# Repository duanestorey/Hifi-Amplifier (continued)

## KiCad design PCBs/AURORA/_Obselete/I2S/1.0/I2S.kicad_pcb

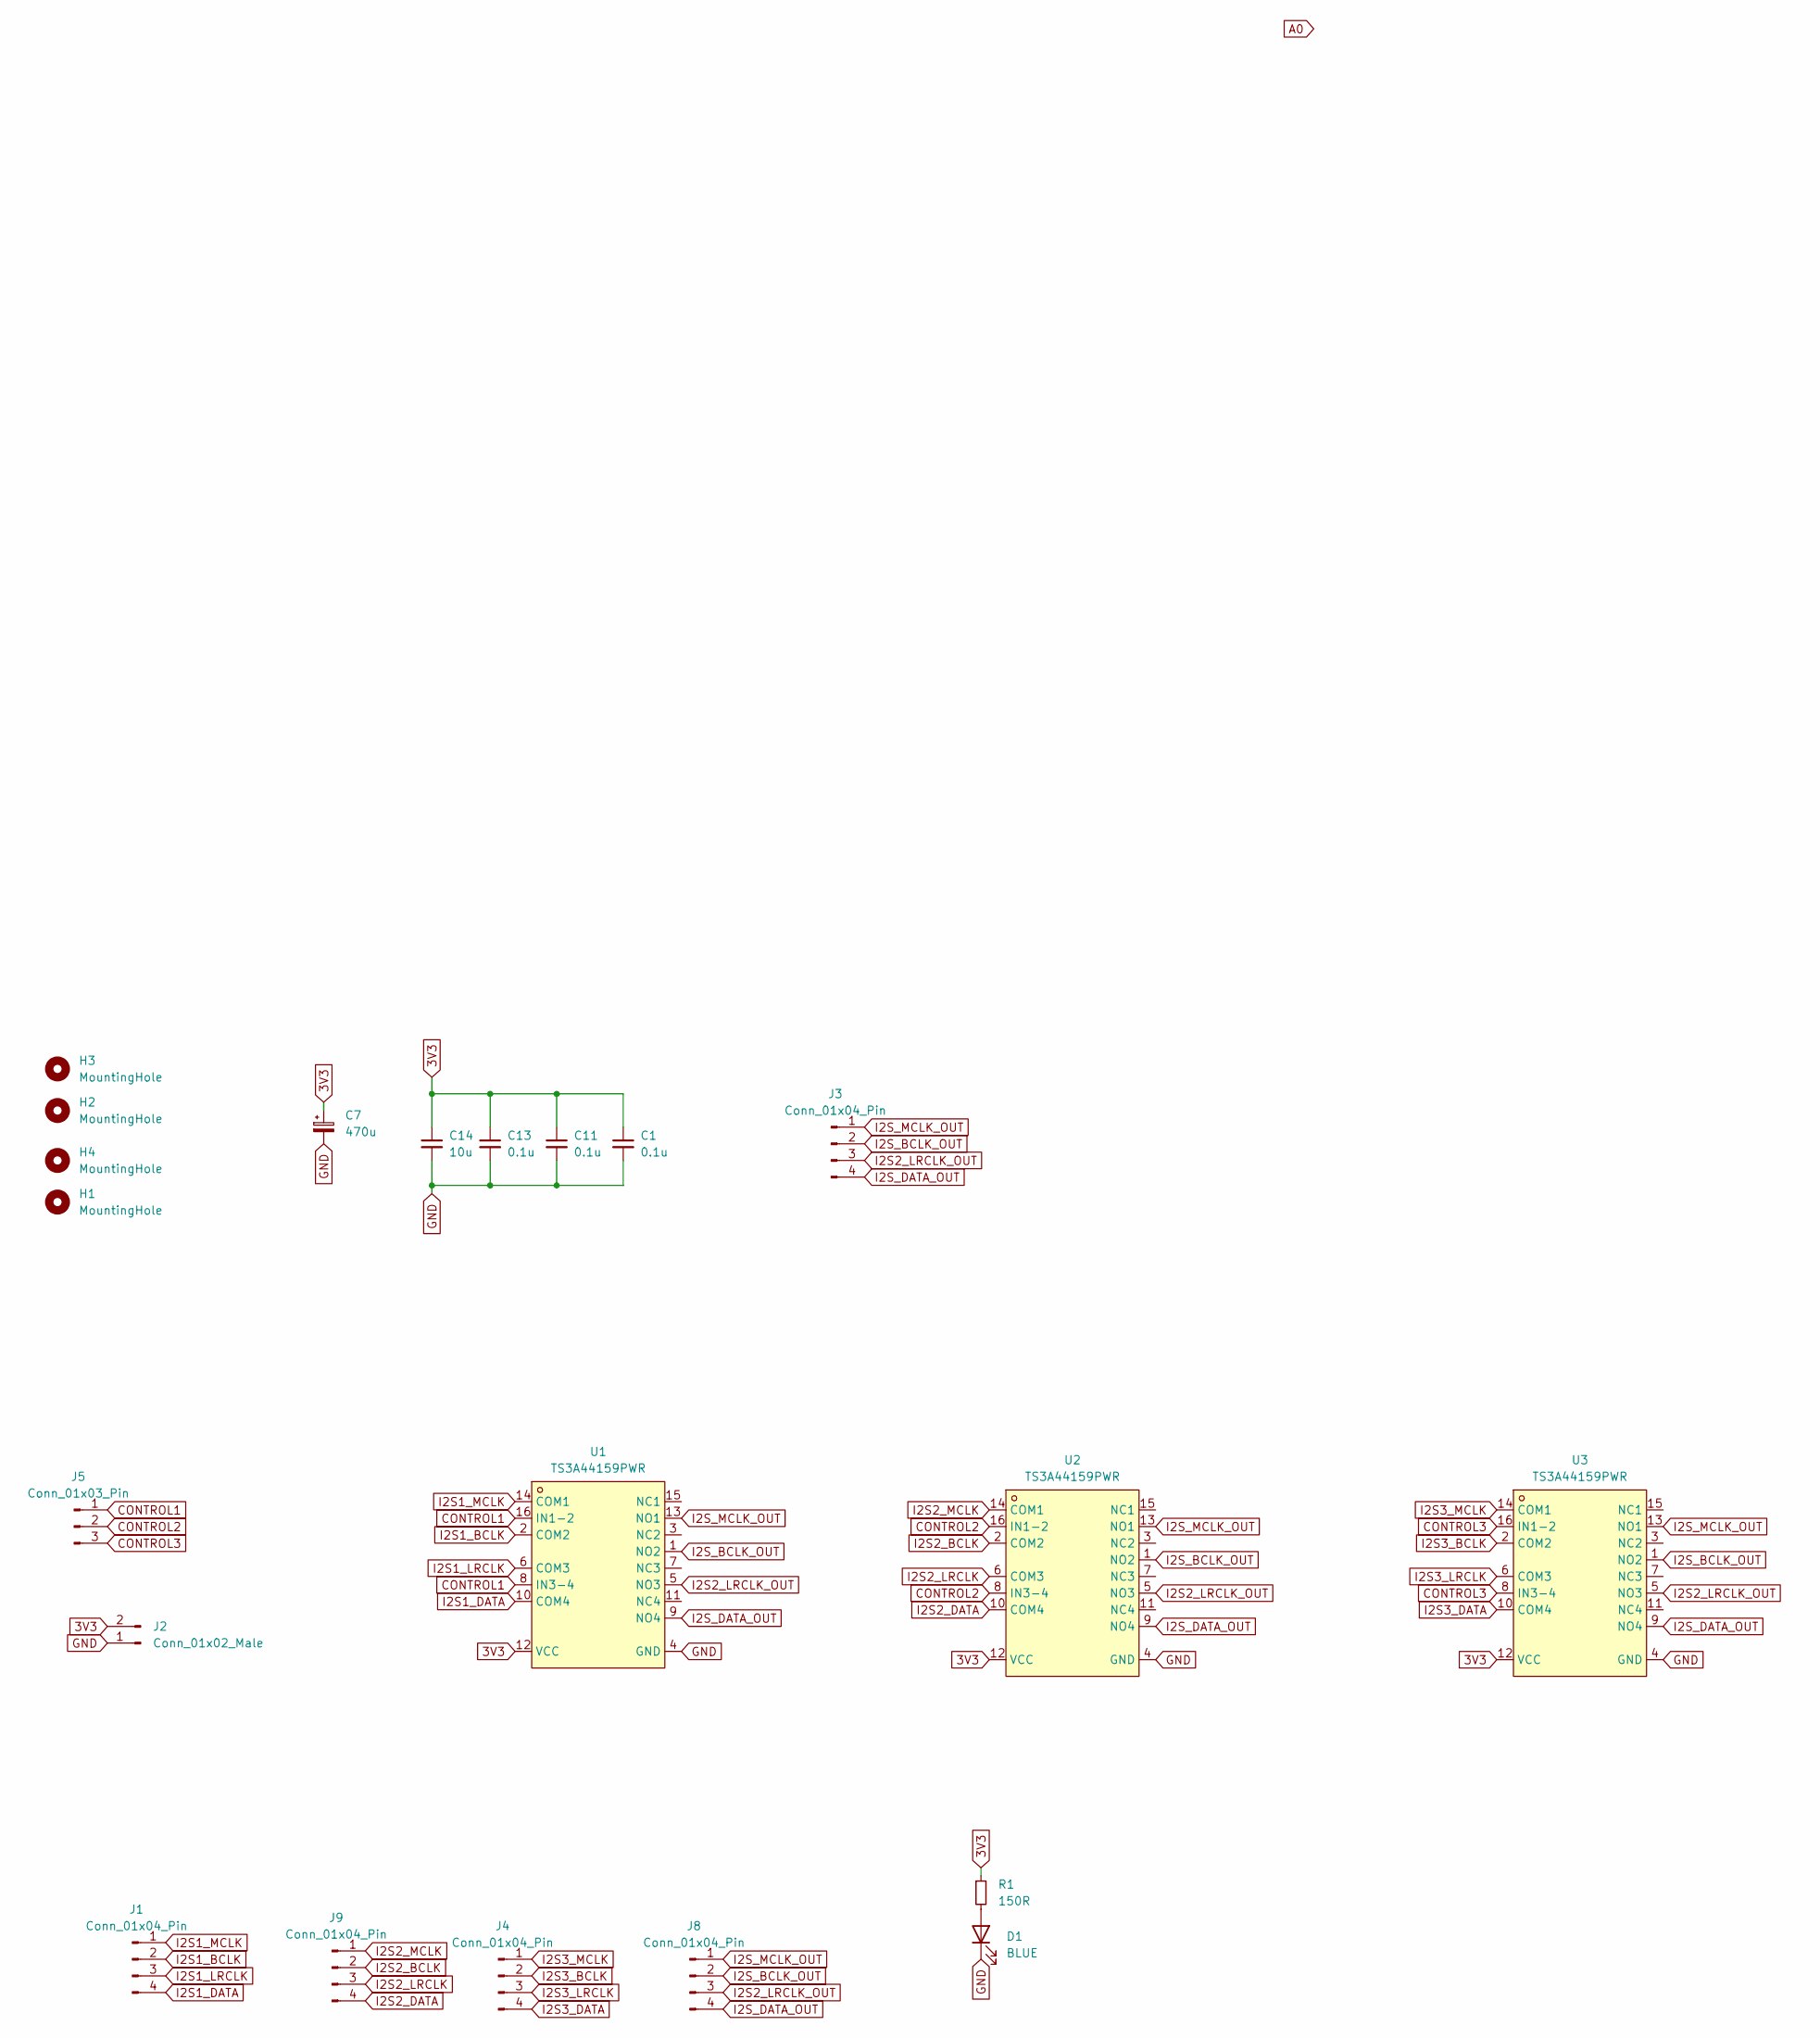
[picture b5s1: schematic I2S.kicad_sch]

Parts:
C1, C11, C13: 0.1u; C_0805_2012Metric_Pad1.18x1.45mm_HandSolder
C7: 470u; CP_Radial_D6.3mm_P2.50mm
C14: 10u; C_1206_3216Metric_Pad1.33x1.80mm_HandSolder
D1: BLUE; LED_0603_1608Metric
H1, H2, H3, H4: MountingHole; MountingHole_3.2mm_M3_DIN965_Pad_TopOnly
J1, J4, J8, J9: Conn_01x04_Pin; JST_PH_B4B-PH-K_1x04_P2.00mm_Vertical
J2: Conn_01x02_Male; JST_PH_B2B-PH-K_1x02_P2.00mm_Vertical
J3: Conn_01x04_Pin; PinHeader_1x04_P2.54mm_Vertical
J5: Conn_01x03_Pin; JST_PH_B3B-PH-K_1x03_P2.00mm_Vertical
R1: 150R; R_0603_1608Metric
U1, U2, U3: TS3A44159PWR; TSSOP-16_L5.0-W4.4-P0.65-LS6.4-BL; LCSC Part C151886

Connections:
3V3: C1.1, C7.1, C11.1, C13.1, C14.1, J2.2, R1.1, U1.12 (VCC), U2.12 (VCC), U3.12 (VCC)
CONTROL1: J5.1, U1.8 (IN3-4), U1.16 (IN1-2)
CONTROL2: J5.2, U2.8 (IN3-4), U2.16 (IN1-2)
CONTROL3: J5.3, U3.8 (IN3-4), U3.16 (IN1-2)
GND: C1.2, C7.2, C11.2, C13.2, C14.2, D1.1 (K), J2.1, U1.4 (GND), U2.4 (GND), U3.4 (GND)
I2S1_BCLK: J1.2, U1.2 (COM2)
I2S1_DATA: J1.4, U1.10 (COM4)
I2S1_LRCLK: J1.3, U1.6 (COM3)
I2S1_MCLK: J1.1, U1.14 (COM1)
I2S2_BCLK: J9.2, U2.2 (COM2)
I2S2_DATA: J9.4, U2.10 (COM4)
I2S2_LRCLK: J9.3, U2.6 (COM3)
I2S2_LRCLK_OUT: J3.3, J8.3, U1.5 (NO3), U2.5 (NO3), U3.5 (NO3)
I2S2_MCLK: J9.1, U2.14 (COM1)
I2S3_BCLK: J4.2, U3.2 (COM2)
I2S3_DATA: J4.4, U3.10 (COM4)
I2S3_LRCLK: J4.3, U3.6 (COM3)
I2S3_MCLK: J4.1, U3.14 (COM1)
I2S_BCLK_OUT: J3.2, J8.2, U1.1 (NO2), U2.1 (NO2), U3.1 (NO2)
I2S_DATA_OUT: J3.4, J8.4, U1.9 (NO4), U2.9 (NO4), U3.9 (NO4)
I2S_MCLK_OUT: J3.1, J8.1, U1.13 (NO1), U2.13 (NO1), U3.13 (NO1)
unnamed: D1.2 (A), R1.2

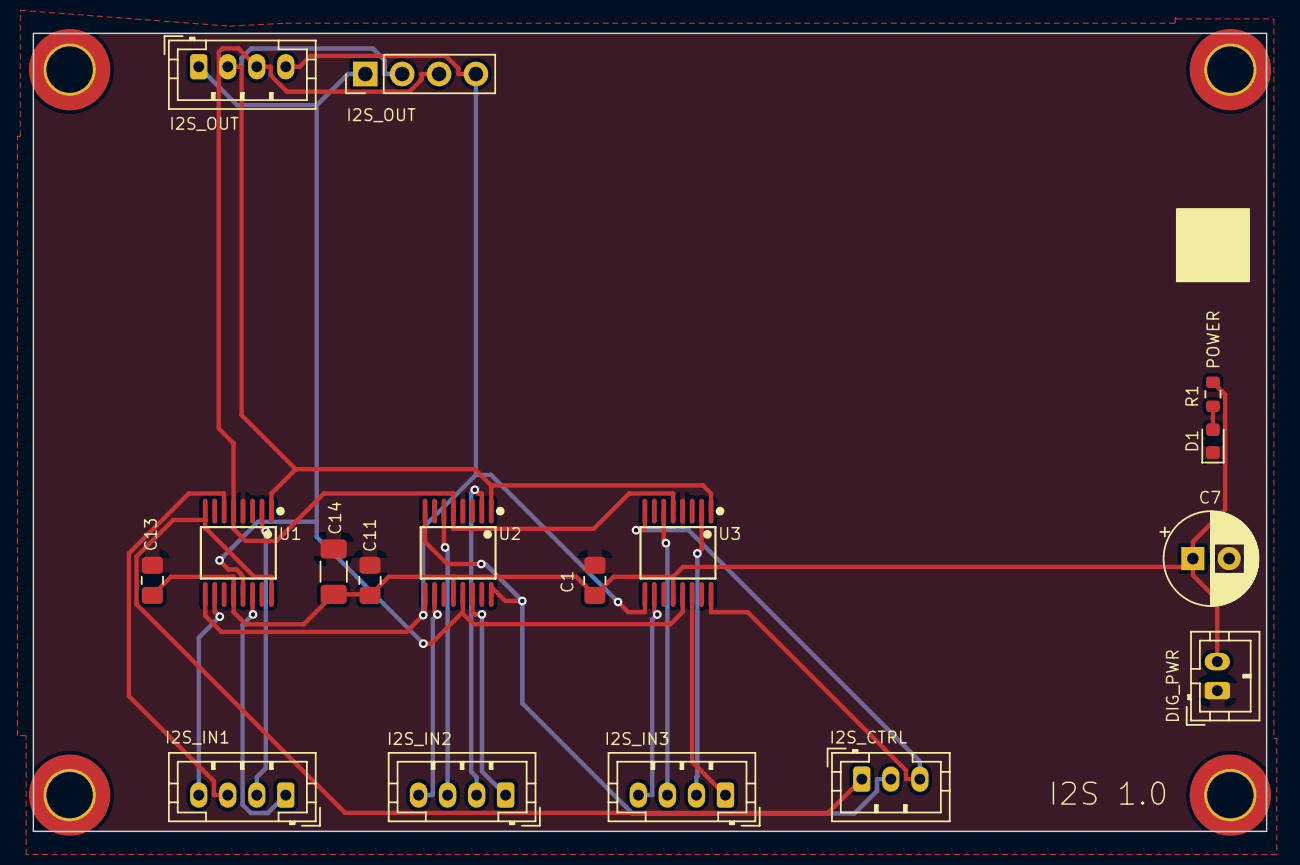
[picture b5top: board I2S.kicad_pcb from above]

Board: 2 copper layers, 85.0 x 55.0 mm, 21 parts (0 on the bottom side), 22 nets.

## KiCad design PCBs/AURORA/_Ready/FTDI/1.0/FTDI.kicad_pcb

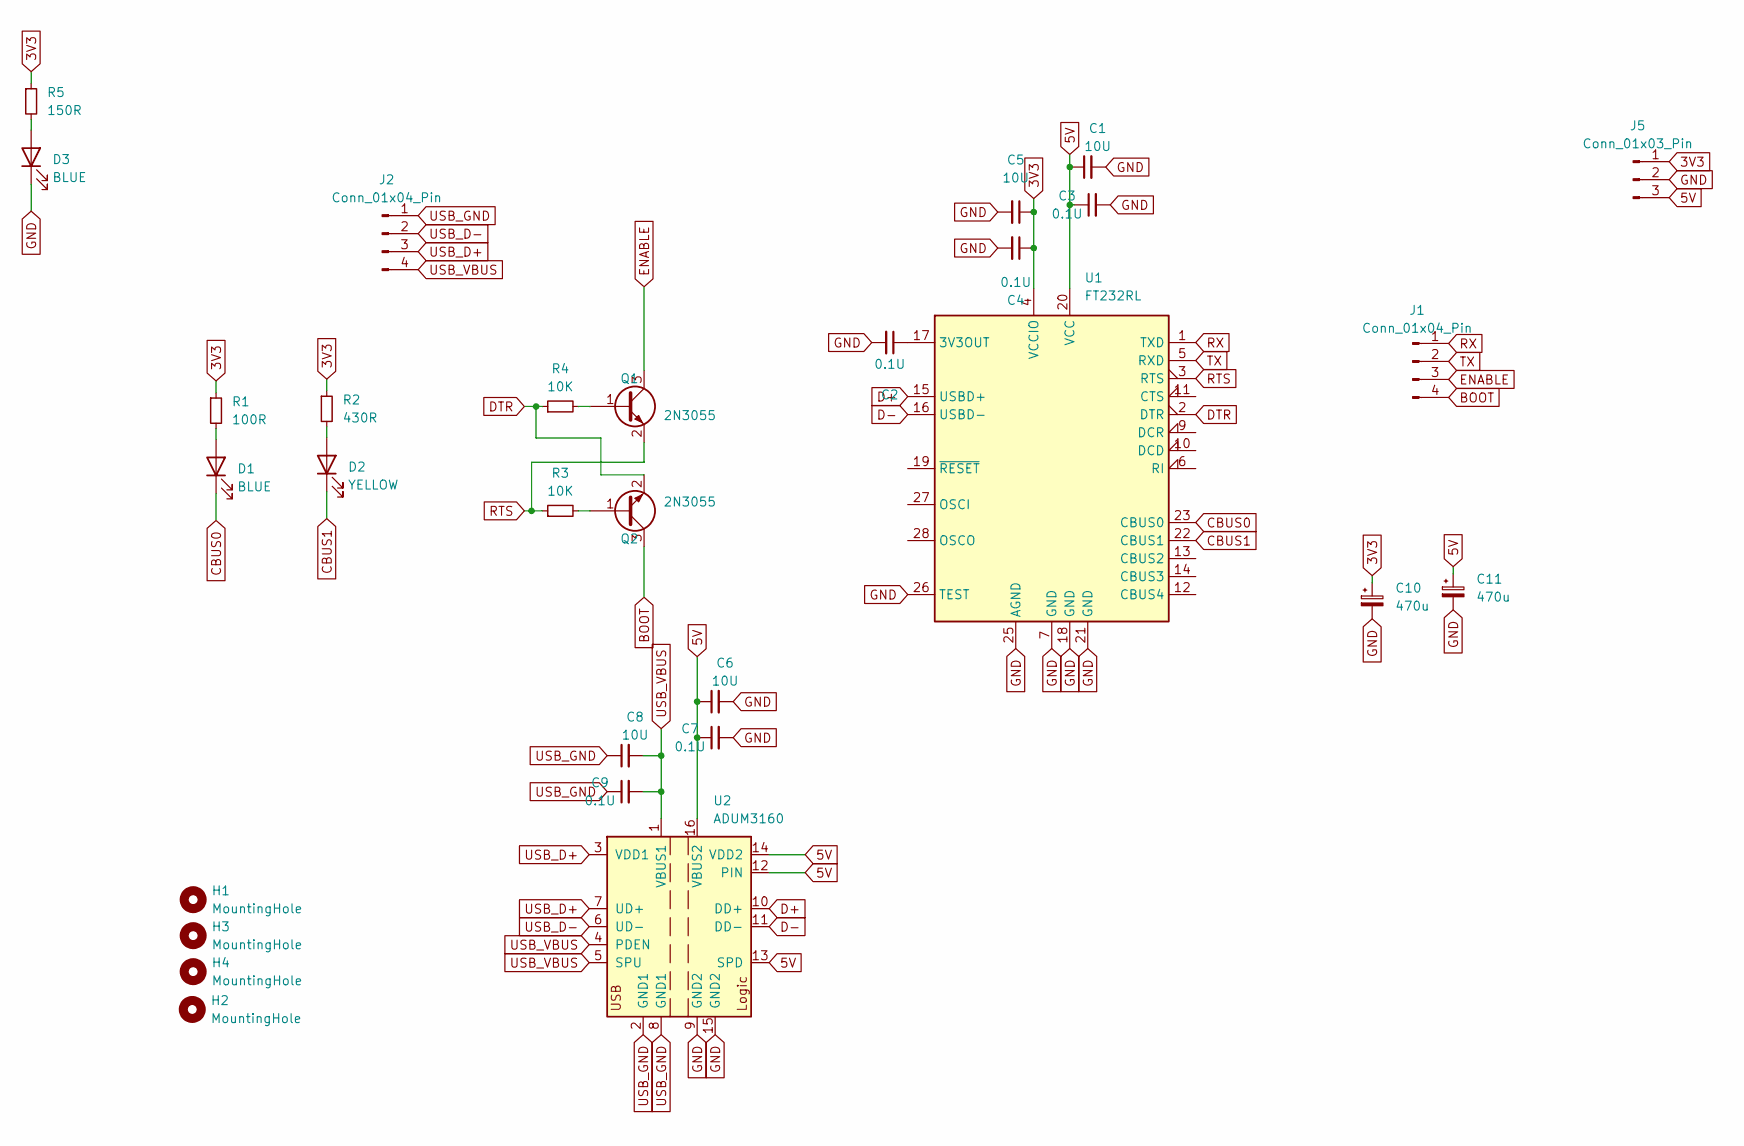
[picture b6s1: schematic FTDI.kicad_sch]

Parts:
C1, C5, C6, C8: 10U; C_1206_3216Metric_Pad1.33x1.80mm_HandSolder
C2, C3, C4, C7, C9: 0.1U; C_0805_2012Metric_Pad1.18x1.45mm_HandSolder
C10, C11: 470u; CP_Radial_D6.3mm_P2.50mm
D1, D3: BLUE; LED_0603_1608Metric_Pad1.05x0.95mm_HandSolder; LCSC XL-1608UBC-04
D2: YELLOW; LED_0603_1608Metric_Pad1.05x0.95mm_HandSolder; LCSC XL-1608UBC-04
H1, H2, H3, H4: MountingHole; MountingHole_3.2mm_M3_DIN965_Pad_TopOnly
J1, J2: Conn_01x04_Pin; JST_PH_B4B-PH-K_1x04_P2.00mm_Vertical
J5: Conn_01x03_Pin; JST_PH_B3B-PH-K_1x03_P2.00mm_Vertical
Q1, Q2: 2N3055; TSOT-23
R1: 100R; R_0603_1608Metric_Pad0.98x0.95mm_HandSolder
R2: 430R; R_0603_1608Metric_Pad0.98x0.95mm_HandSolder
R3, R4: 10K; R_0603_1608Metric_Pad0.98x0.95mm_HandSolder
R5: 150R; R_0603_1608Metric_Pad0.98x0.95mm_HandSolder
U1: FT232RL; SSOP-28_5.3x10.2mm_P0.65mm
U2: ADUM3160; SOIC-16W_7.5x10.3mm_P1.27mm; Mouser 584-ADUM3160BRWZ-R

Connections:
3V3: C4.1, C5.1, C10.1, J5.1, R1.1, R2.1, R5.1, U1.4 (VCCIO)
5V: C1.1, C3.1, C6.1, C7.1, C11.1, J5.3, U1.20 (VCC), U2.12 (PIN), U2.13 (SPD), U2.14 (VDD2), U2.16 (VBUS2)
BOOT: J1.4, Q2.3 (C)
CBUS0: D1.1 (K), U1.23 (CBUS0)
CBUS1: D2.1 (K), U1.22 (CBUS1)
D+: U1.15 (USBD+), U2.10 (DD+)
D-: U1.16 (USBD-), U2.11 (DD-)
DTR: Q2.2 (E), R4.1, U1.2 (DTR)
ENABLE: J1.3, Q1.3 (C)
GND: C1.2, C2.2, C3.2, C4.2, C5.2, C6.2, C7.2, C10.2, C11.2, D3.1 (K), J5.2, U1.7 (GND), U1.18 (GND), U1.21 (GND), U1.25 (AGND), U1.26 (TEST), U2.9 (GND2), U2.15 (GND2)
unnamed: D1.2 (A), R1.2
unnamed: D2.2 (A), R2.2
unnamed: D3.2 (A), R5.2
unnamed: Q1.1 (B), R4.2
unnamed: Q2.1 (B), R3.2
unnamed: C2.1, U1.17 (3V3OUT)
RTS: Q1.2 (E), R3.1, U1.3 (RTS)
RX: J1.1, U1.1 (TXD)
TX: J1.2, U1.5 (RXD)
USB_D+: J2.3, U2.3 (VDD1), U2.7 (UD+)
USB_D-: J2.2, U2.6 (UD-)
USB_GND: C8.1, C9.1, J2.1, U2.2 (GND1), U2.8 (GND1)
USB_VBUS: C8.2, C9.2, J2.4, U2.1 (VBUS1), U2.4 (PDEN), U2.5 (SPU)

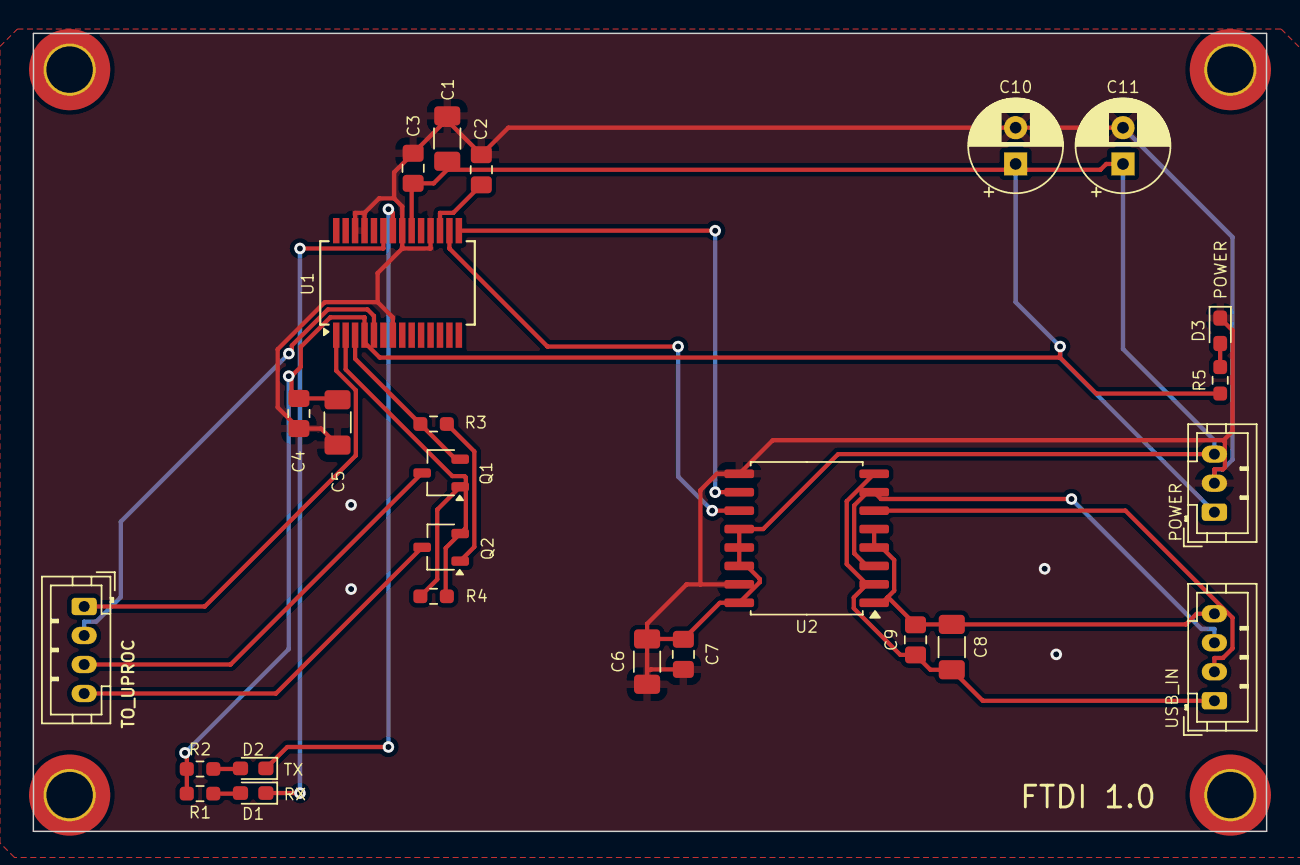
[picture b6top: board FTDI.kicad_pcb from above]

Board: 2 copper layers, 85.0 x 55.0 mm, 30 parts (0 on the bottom side), 23 nets.

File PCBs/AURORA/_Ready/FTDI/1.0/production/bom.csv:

Designator,Footprint,Quantity,Value,LCSC Part #
"C1, C5, C6, C8",1206,4,10U,
"C10, C11",CP_Radial_D6.3mm_P2.50mm,2,470u,
"C2, C3, C4, C7, C9",0805,5,0.1U,
"D1, D3",0603,2,BLUE,XL-1608UBC-04
D2,0603,1,YELLOW,XL-1608UBC-04
"H1, H2, H3, H4",MountingHole_3.2mm_M3_DIN965_Pad_TopOnly,4,MountingHole,
"J1, J2",JST_PH_B4B-PH-K_1x04_P2.00mm_Vertical,2,Conn_01x04_Pin,
J5,JST_PH_B3B-PH-K_1x03_P2.00mm_Vertical,1,Conn_01x03_Pin,
"Q1, Q2",TSOT-23,2,2N3055,
R1,0603,1,100R,
R2,0603,1,430R,
"R3, R4",0603,2,10K,
R5,0603,1,150R,
U1,SSOP-28_5.3x10.2mm_P0.65mm,1,FT232RL,
U2,SOIC-16W_7.5x10.3mm_P1.27mm,1,ADUM3160,

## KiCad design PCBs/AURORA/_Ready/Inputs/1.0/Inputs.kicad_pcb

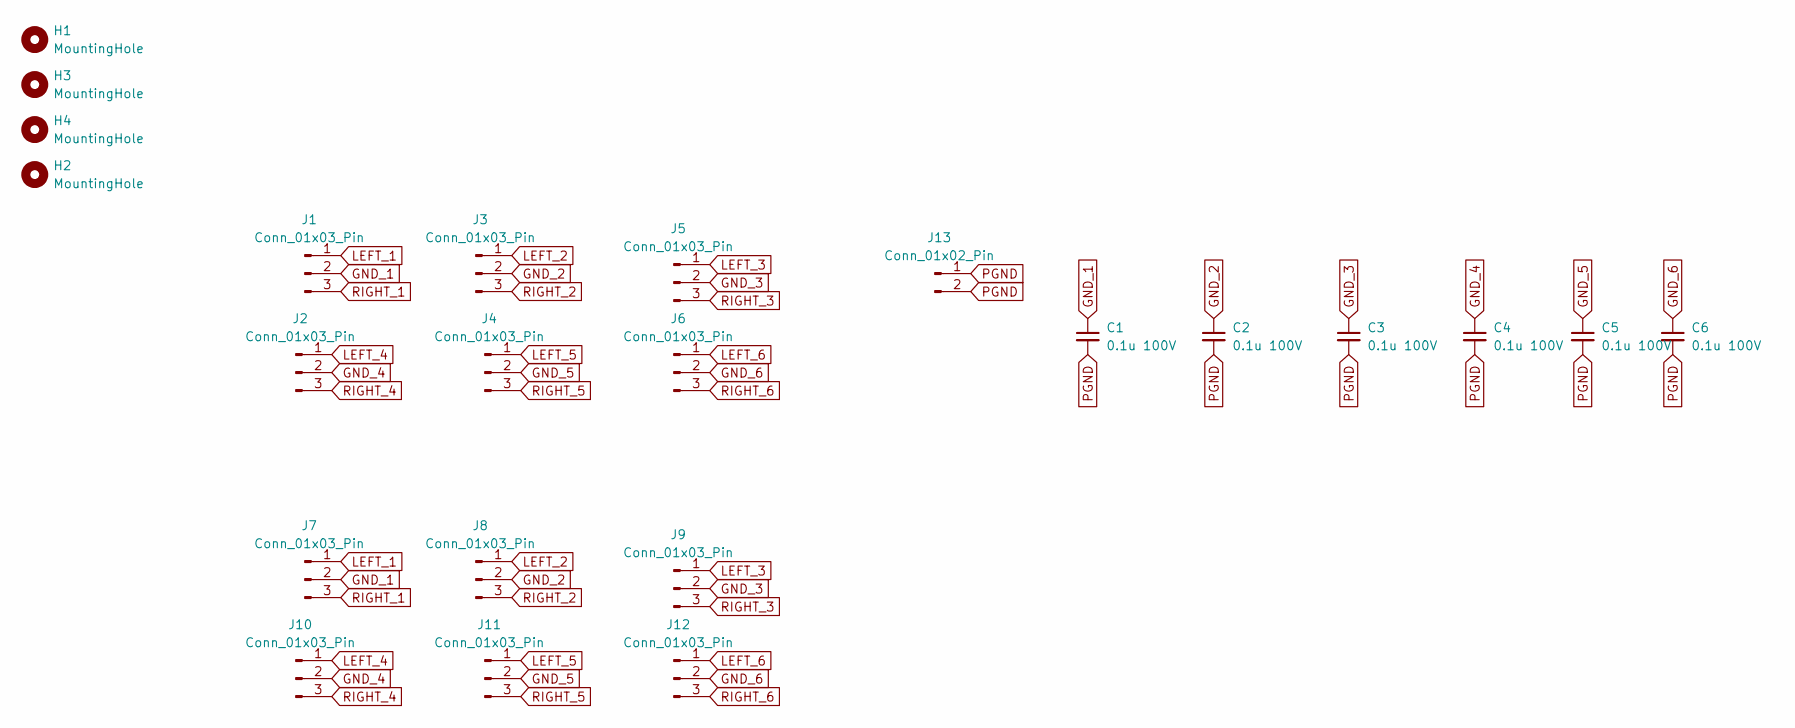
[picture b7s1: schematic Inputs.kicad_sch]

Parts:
C1, C2, C3, C4, C5, C6: 0.1u 100V; C_1206_3216Metric; Mouser 791-1206B104K101CT
H1, H2, H3, H4: MountingHole; MountingHole_3.2mm_M3_DIN965_Pad_TopOnly
J1, J2, J3, J4, J5, J6, J7, J8, J9, J10, J11, J12: Conn_01x03_Pin; JST_PH_B3B-PH-K_1x03_P2.00mm_Vertical
J13: Conn_01x02_Pin; JST_VH_B2P-VH-B_1x02_P3.96mm_Vertical

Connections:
GND_1: C1.1, J1.2, J7.2
GND_2: C2.1, J3.2, J8.2
GND_3: C3.1, J5.2, J9.2
GND_4: C4.1, J2.2, J10.2
GND_5: C5.1, J4.2, J11.2
GND_6: C6.1, J6.2, J12.2
LEFT_1: J1.1, J7.1
LEFT_2: J3.1, J8.1
LEFT_3: J5.1, J9.1
LEFT_4: J2.1, J10.1
LEFT_5: J4.1, J11.1
LEFT_6: J6.1, J12.1
PGND: C1.2, C2.2, C3.2, C4.2, C5.2, C6.2, J13.1, J13.2
RIGHT_1: J1.3, J7.3
RIGHT_2: J3.3, J8.3
RIGHT_3: J5.3, J9.3
RIGHT_4: J2.3, J10.3
RIGHT_5: J4.3, J11.3
RIGHT_6: J6.3, J12.3

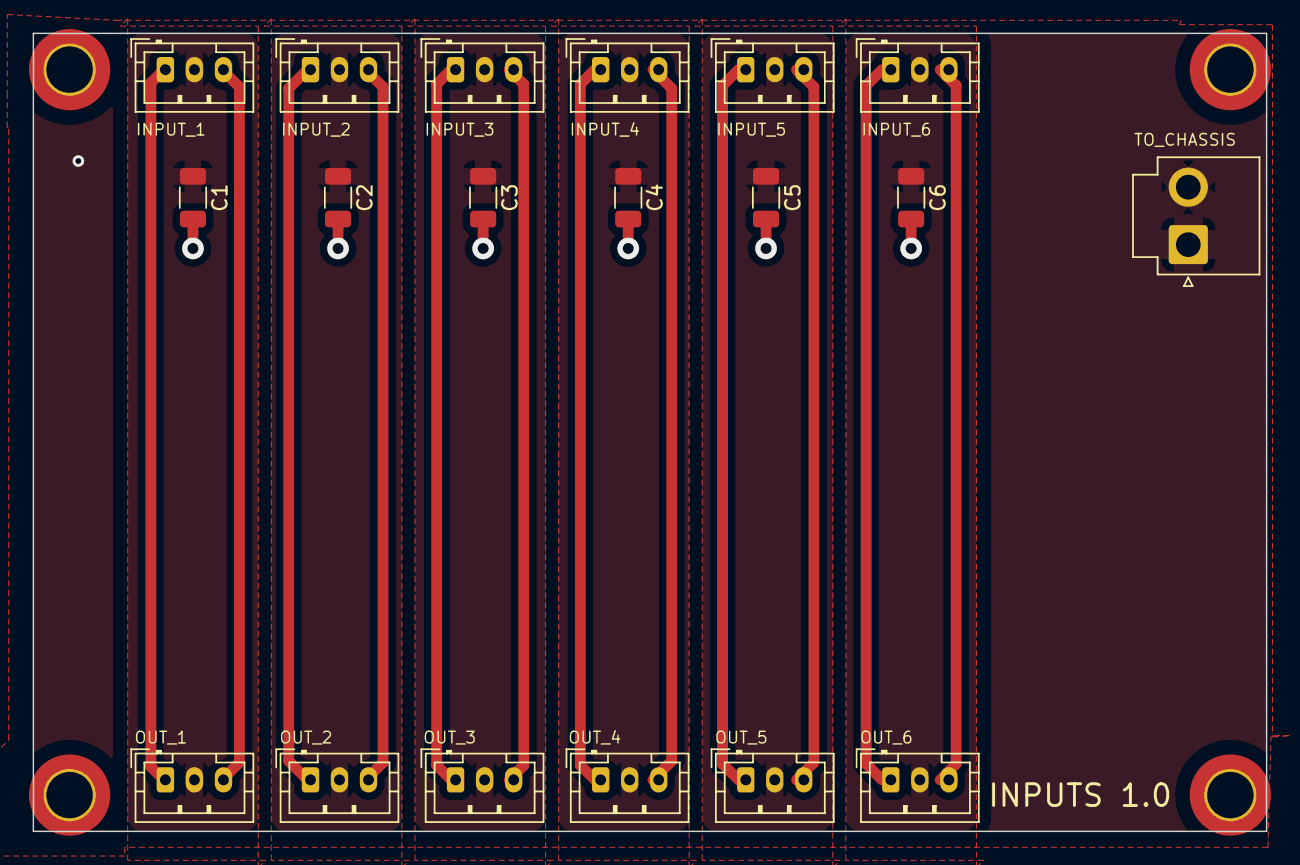
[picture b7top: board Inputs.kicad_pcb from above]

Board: 2 copper layers, 85.0 x 55.0 mm, 23 parts (0 on the bottom side), 19 nets.

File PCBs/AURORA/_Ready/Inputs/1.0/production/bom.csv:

Designator,Footprint,Quantity,Value,LCSC Part #
"C1, C2, C3, C4, C5, C6",1206,6,0.1u 100V,
"H1, H2, H3, H4",MountingHole_3.2mm_M3_DIN965_Pad_TopOnly,4,MountingHole,
"J1, J10, J11, J12, J2, J3, J4, J5, J6, J7, J8, J9",JST_PH_B3B-PH-K_1x03_P2.00mm_Vertical,12,Conn_01x03_Pin,
J13,JST_VH_B2P-VH-B_1x02_P3.96mm_Vertical,1,Conn_01x02_Pin,

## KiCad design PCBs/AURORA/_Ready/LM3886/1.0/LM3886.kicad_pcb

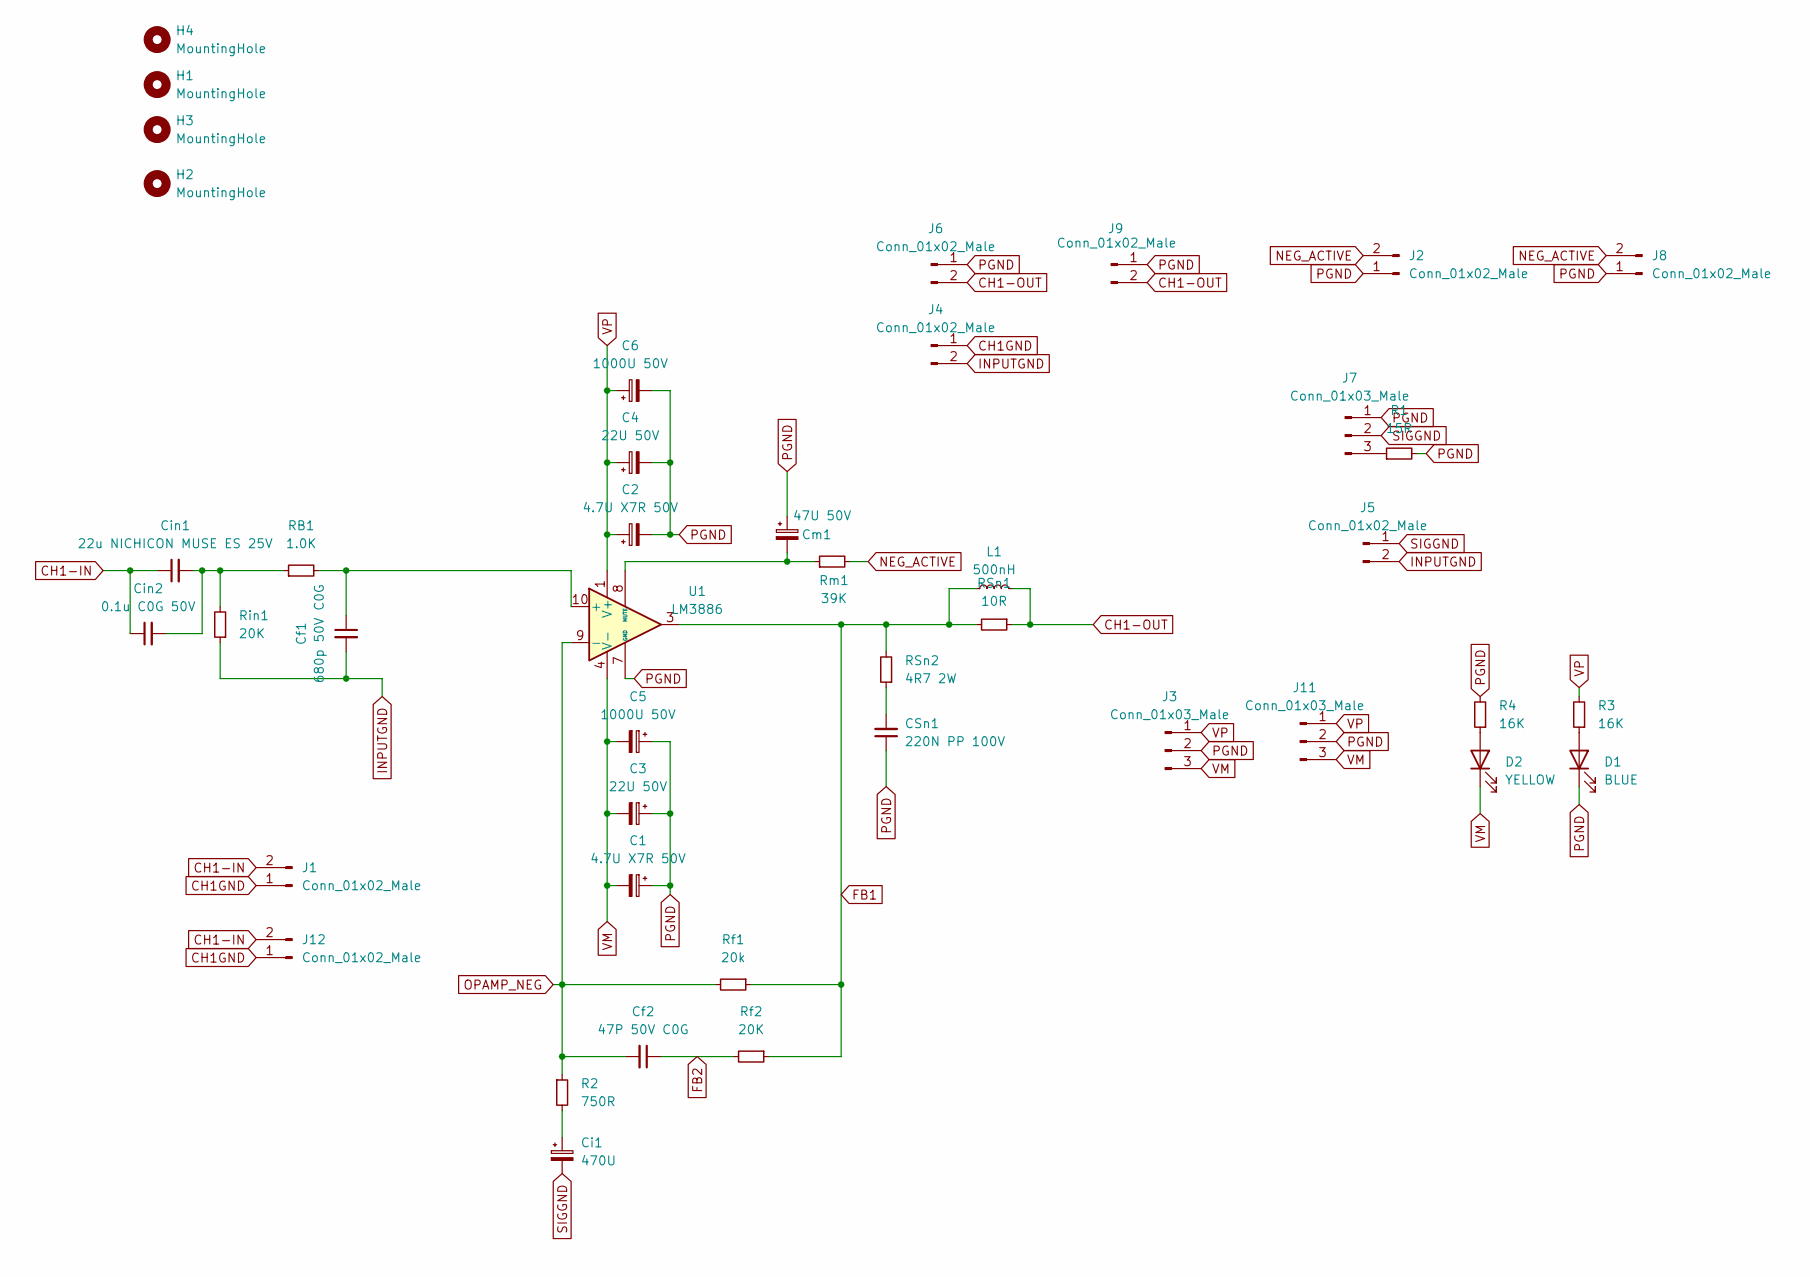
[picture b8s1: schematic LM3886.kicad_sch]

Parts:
C1, C2: 4.7U X7R 50V; C_1206_3216Metric_Pad1.33x1.80mm_HandSolder; Mouser 80-C1206X475J5RACTU
C3, C4: 22U 50V; CP_Radial_D6.3mm_P2.50mm
C5, C6: 1000U 50V; CP_Radial_D12.5mm_P5.00mm
CSn1: 220N PP 100V; C_Rect_L18.0mm_W7.0mm_P15.00mm_FKS3_FKP3; Mouser 505-MKP1D032204D00JB
Cf1: 680p 50V C0G; C_1206_3216Metric_Pad1.33x1.80mm_HandSolder; Mouser 603-CC126GRNPO9BN681
Cf2: 47P 50V C0G; C_1206_3216Metric_Pad1.33x1.80mm_HandSolder; Mouser 791-1206N470F500CT
Ci1: 470U; CP_Radial_D12.5mm_P5.00mm
Cin1: 22u NICHICON MUSE ES 25V; C_Radial_D6.3mm_H5.0mm_P2.50mm
Cin2: 0.1u C0G 50V; C_1206_3216Metric_Pad1.33x1.80mm_HandSolder; Mouser 81-GRT31C5C1H104FA2L
Cm1: 47U 50V; CP_Radial_D6.3mm_P2.50mm
D1: BLUE; LED_0603_1608Metric_Pad1.05x0.95mm_HandSolder
D2: YELLOW; LED_0603_1608Metric_Pad1.05x0.95mm_HandSolder
H1, H2, H3, H4: MountingHole; M3 Slot
J1, J2, J8, J12: Conn_01x02_Male; JST_PH_B2B-PH-K_1x02_P2.00mm_Vertical
J3, J11: Conn_01x03_Male; JST_VH_B3P-VH-B_1x03_P3.96mm_Vertical
J4, J5: Conn_01x02_Male; PinHeader_1x02_P2.54mm_Vertical
J6, J9: Conn_01x02_Male; JST_VH_B2P-VH_1x02_P3.96mm_Vertical
J7: Conn_01x03_Male; PinHeader_1x03_P2.54mm_Vertical
L1: 500nH; 500nH Inductor Aliexpress Air Gap
R1: 15R; R_1206_3216Metric_Pad1.30x1.75mm_HandSolder
R2: 750R; R_1206_3216Metric_Pad1.30x1.75mm_HandSolder; Mouser 603-RT1206FRE07750RL
R3, R4: 16K; R_0603_1608Metric_Pad0.98x0.95mm_HandSolder
RB1: 1.0K; R_1206_3216Metric_Pad1.30x1.75mm_HandSolder; Mouser 603-RT1206FRE131KL
RSn1: 10R; R_4020_10251Metric_Pad1.65x5.30mm_HandSolder; Mouser 279-355010RJT
RSn2: 4R7 2W; R_2512_6332Metric_Pad1.40x3.35mm_HandSolder; Mouser 603-RC2512JK-7W4R7
Rf1: 20k; R_1206_3216Metric_Pad1.30x1.75mm_HandSolder; Mouser 603-RT1206FRD0720KL
Rf2: 20K; R_1206_3216Metric_Pad1.30x1.75mm_HandSolder; Mouser 603-RT1206FRD0720KL
Rin1: 20K; R_1206_3216Metric_Pad1.30x1.75mm_HandSolder; Mouser 603-RT1206FRD0720KL
Rm1: 39K; R_1206_3216Metric_Pad1.30x1.75mm_HandSolder; Mouser 603-RC1206JR-0739KL
U1: LM3886; TO-220-11_P3.4x5.08mm_StaggerOdd_Lead4.85mm_Vertical

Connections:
CH1-IN: Cin1.1, Cin2.1, J1.2, J12.2
CH1-OUT: J6.2, J9.2, L1.2, RSn1.1
CH1GND: J1.1, J4.1, J12.1
FB1: L1.1, RSn1.2, RSn2.2, Rf1.1, Rf2.1, U1.3
FB2: Cf2.1, Rf2.2
INPUTGND: Cf1.2, J4.2, J5.2, Rin1.1
NEG_ACTIVE: J2.2, J8.2, Rm1.2
unnamed: CSn1.2, RSn2.1
unnamed: Ci1.1, R2.2
unnamed: Cin1.2, Cin2.2, RB1.1, Rin1.2
unnamed: D1.2 (A), R3.1
unnamed: D2.2 (A), R4.1
unnamed: J7.3, R1.1
unnamed: Cf1.1, RB1.2, U1.10 (+)
unnamed: Cm1.2, Rm1.1, U1.8 (MUTE)
OPAMP_NEG: Cf2.2, R2.1, Rf1.2, U1.9 (-)
PGND: C1.1, C2.2, C3.1, C4.2, C5.1, C6.2, CSn1.1, Cm1.1, D1.1 (K), J2.1, J3.2, J6.1, J7.1, J8.1, J9.1, J11.2, R1.2, R4.2, U1.7 (GND)
SIGGND: Ci1.2, J5.1, J7.2
VM: C1.2, C3.2, C5.2, D2.1 (K), J3.3, J11.3, U1.4 (V-)
VP: C2.1, C4.1, C6.1, J3.1, J11.1, R3.2, U1.1 (V+), U1.5 (V+)

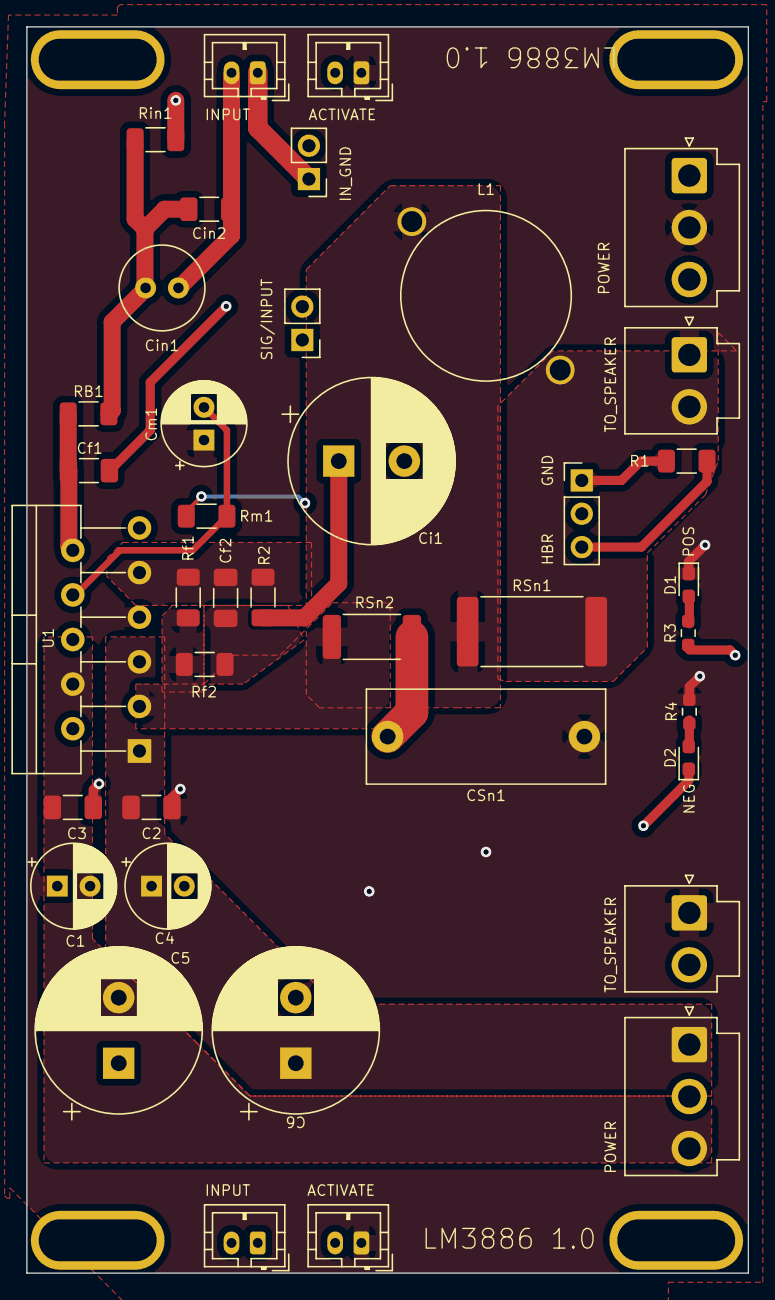
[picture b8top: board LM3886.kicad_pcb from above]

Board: 4 copper layers, 55.0 x 95.0 mm, 43 parts (0 on the bottom side), 20 nets.

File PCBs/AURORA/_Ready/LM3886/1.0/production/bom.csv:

Designator,Footprint,Quantity,Value,LCSC Part #
"C1, C2",1206,2,4.7U X7R 50V,
"C3, C4",CP_Radial_D6.3mm_P2.50mm,2,22U 50V,
"C5, C6",CP_Radial_D12.5mm_P5.00mm,2,1000U 50V,
CF1,1206,1,680p 50V C0G,
CF2,1206,1,47P 50V C0G,
CI1,CP_Radial_D12.5mm_P5.00mm,1,470U,
CIN1,C_Radial_D6.3mm_H5.0mm_P2.50mm,1,22u NICHICON MUSE ES 25V,
CIN2,1206,1,0.1u C0G 50V,
CM1,CP_Radial_D6.3mm_P2.50mm,1,47U 50V,
CSN1,C_Rect_L18.0mm_W7.0mm_P15.00mm_FKS3_FKP3,1,220N PP 100V,
D1,0603,1,BLUE,
D2,0603,1,YELLOW,
"H1, H2, H3, H4",M3 Slot,4,MountingHole,
"J1, J12, J2, J8",JST_PH_B2B-PH-K_1x02_P2.00mm_Vertical,4,Conn_01x02_Male,
"J11, J3",JST_VH_B3P-VH-B_1x03_P3.96mm_Vertical,2,Conn_01x03_Male,
"J4, J5",PinHeader_1x02_P2.54mm_Vertical,2,Conn_01x02_Male,
"J6, J9",JST_VH_B2P-VH_1x02_P3.96mm_Vertical,2,Conn_01x02_Male,
J7,PinHeader_1x03_P2.54mm_Vertical,1,Conn_01x03_Male,
L1,500nH Inductor Aliexpress Air Gap,1,500nH,
R1,1206,1,15R,
R2,1206,1,750R,
"R3, R4",0603,2,16K,
RB1,1206,1,1.0K,
"RF1, RF2, RIN1",1206,3,20k,
RM1,1206,1,39K,
RSN1,4020,1,10R,
RSN2,2512,1,4R7 2W,
U1,TO-220-11_P3.4x5.08mm_StaggerOdd_Lead4.85mm_Vertical,1,LM3886,
